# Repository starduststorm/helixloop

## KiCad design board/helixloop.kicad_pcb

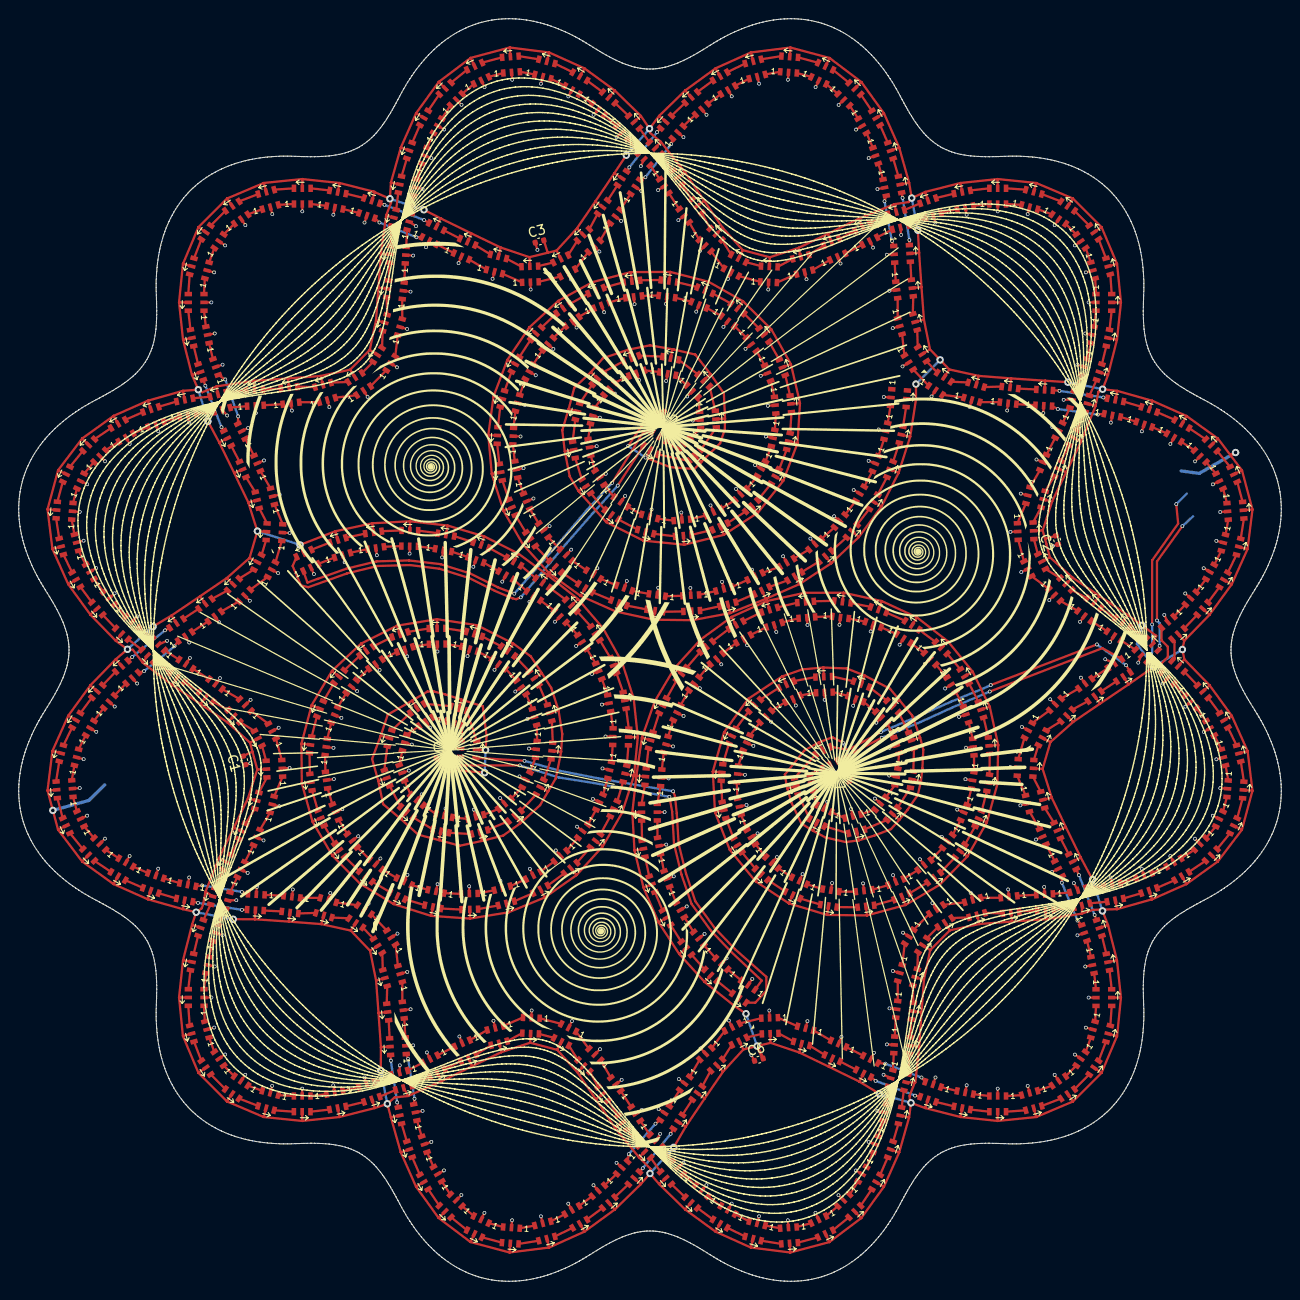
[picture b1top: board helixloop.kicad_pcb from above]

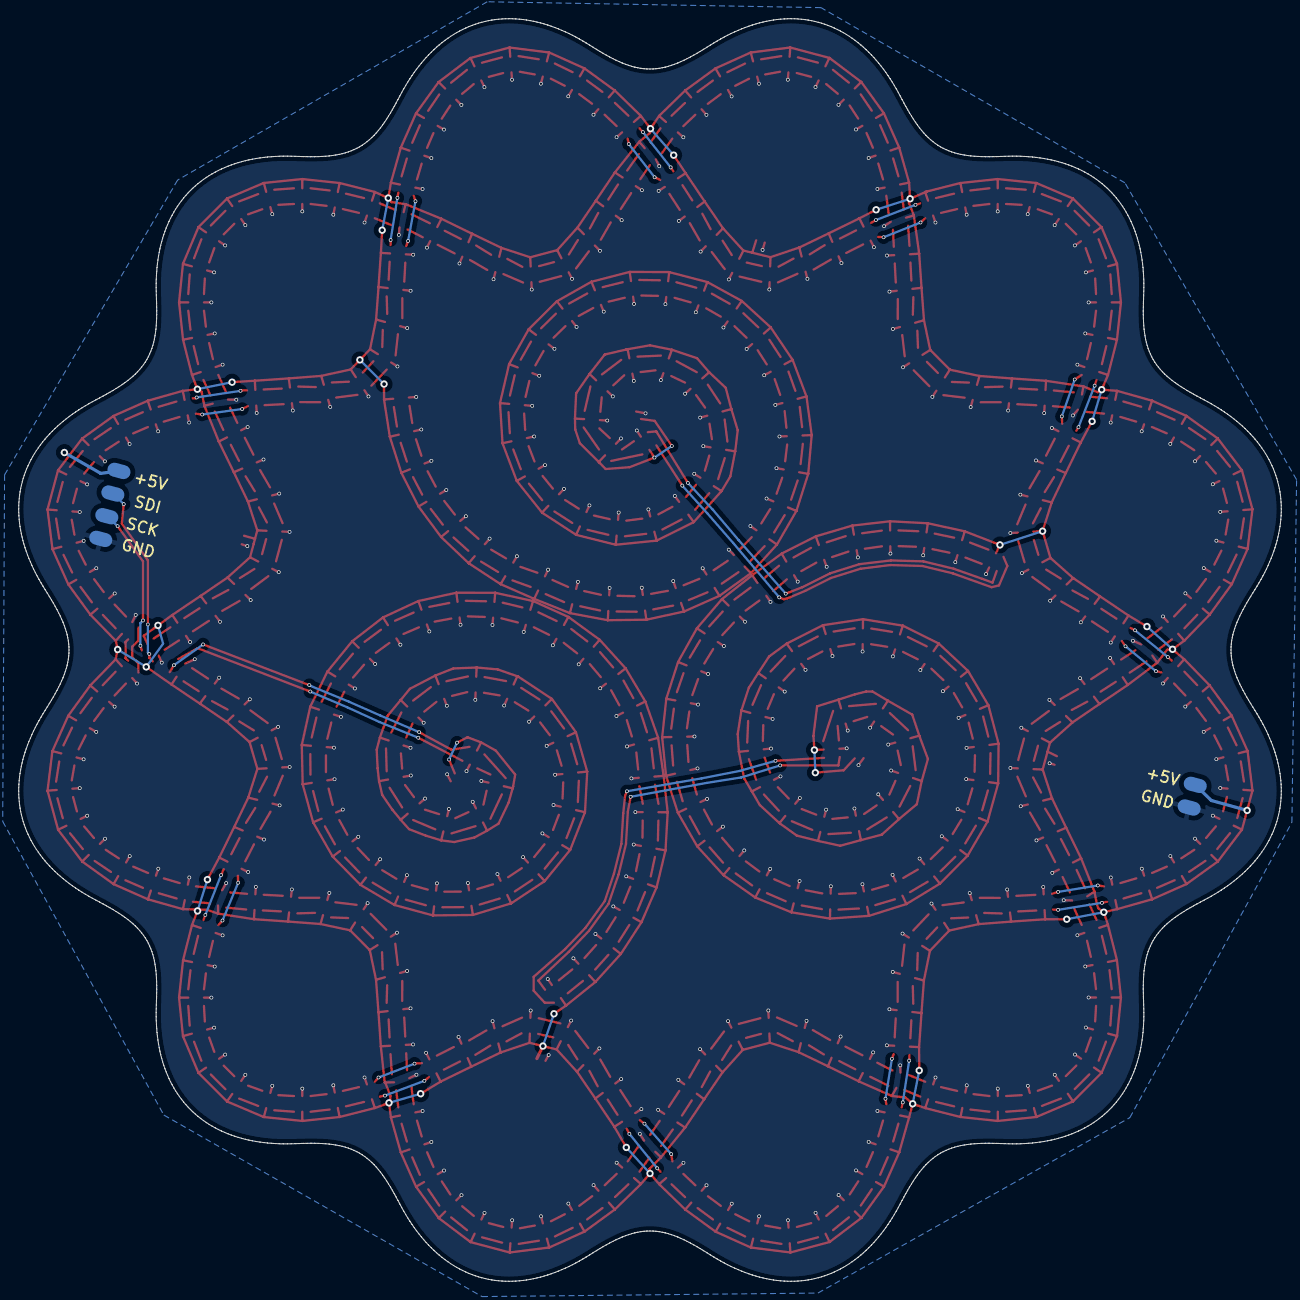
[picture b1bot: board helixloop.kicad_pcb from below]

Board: 2 copper layers, 136.7 x 136.7 mm, 379 parts (2 on the bottom side), 740 nets.

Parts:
C1, C2: 10uF; C_0402_1005Metric
C3, C4, C5, C6, C7: C_Small; C_0402_1005Metric
D1, D2, D3, D4, D5, D6, D7, D8, D9, D10, D11, D12, D13, D14, D15, D16, D17, D18, D19, D20, D21, D22, D23, D24, D25, D26, D27, D28, D29, D30, D31, D32, D33, D34, D35, D36, D37, D38, D39, D40, D41, D42, D43, D44, D45, D46, D47, D48, D49, D50, D51, D52, D53, D54, D55, D56, D57, D58, D59, D60, D61, D62, D63, D64, D65, D66, D67, D68, D69, D70, D71, D72, D73, D74, D75, D76, D77, D78, D79, D80, D81, D82, D83, D84, D85, D86, D87, D88, D89, D90, D91, D92, D93, D94, D95, D96, D97, D98, D99, D100, D101, D102, D103, D104, D105, D106, D107, D108, D109, D110, D111, D112, D113, D114, D115, D116, D117, D118, D119, D120, D121, D122, D123, D124, D125, D126, D127, D128, D129, D130, D131, D132, D133, D134, D135, D136, D137, D138, D139, D140, D141, D142, D143, D144, D145, D146, D147, D148, D149, D150, D151, D152, D153, D154, D155, D156, D157, D158, D159, D160, D161, D162, D163, D164, D165, D166, D167, D168, D169, D170, D171, D172, D173, D174, D175, D176, D177, D178, D179, D180, D181, D182, D183, D184, D185, D186, D187, D188, D189, D190, D191, D192, D193, D194, D195, D196, D197, D198, D199, D200, D201, D202, D203, D204, D205, D206, D207, D208, D209, D210, D211, D212, D213, D214, D215, D216, D217, D218, D219, D220, D221, D222, D223, D224, D225, D226, D227, D228, D229, D230, D231, D232, D233, D234, D235, D236, D237, D238, D239, D240, D241, D242, D243, D244, D245, D246, D247, D248, D249, D250, D251, D252, D253, D254, D255, D256, D257, D258, D259, D260, D261, D262, D263, D264, D265, D266, D267, D268, D269, D270, D271, D272, D273, D274, D275, D276, D277, D278, D279, D280, D281, D282, D283, D284, D285, D286, D287, D288, D289, D290, D291, D292, D293, D294, D295, D296, D297, D298, D299, D300, D301, D302, D303, D304, D305, D306, D307, D308, D309, D310, D311, D312, D313, D314, D315, D316, D317, D318, D319, D320, D321, D322, D323, D324, D325, D326, D327, D328, D329, D330, D331, D332, D333, D334, D335, D336, D337, D338, D339, D340, D341, D342, D343, D344, D345, D346, D347, D348, D349, D350, D351, D352, D353, D354, D355, D356, D357, D358, D359, D360, D361, D362, D363, D364, D365, D366, D367, D368, D369: SK9822-EC20; LED-SK9822-EC20
J1: Conn_01x04; SMD_Pad_01x04_2.54mm
J2: Conn_01x02; SMD_Pad_01x02_2.54mm
spiraldrawing: G***; spiraldrawing

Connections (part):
+5V: C1.2, C2.2, C3.2, C4.2, C5.2, C6.2, C7.2, D1.5 (VDD), D2.5 (VDD), D3.5 (VDD), D4.5 (VDD), D5.5 (VDD), D6.5 (VDD), D7.5 (VDD), D8.5 (VDD), D9.5 (VDD), D10.5 (VDD), D11.5 (VDD), D12.5 (VDD), D13.5 (VDD), D14.5 (VDD), D15.5 (VDD), D16.5 (VDD), D17.5 (VDD), D18.5 (VDD), D19.5 (VDD), D20.5 (VDD), D21.5 (VDD), D22.5 (VDD), D23.5 (VDD), D24.5 (VDD), D25.5 (VDD), D26.5 (VDD), D27.5 (VDD), D28.5 (VDD), D29.5 (VDD), D30.5 (VDD), D31.5 (VDD), D32.5 (VDD), D33.5 (VDD), D34.5 (VDD), D35.5 (VDD), D36.5 (VDD), D37.5 (VDD), D38.5 (VDD), D39.5 (VDD), D40.5 (VDD), D41.5 (VDD), D42.5 (VDD), D43.5 (VDD), D44.5 (VDD), D45.5 (VDD), D46.5 (VDD), D47.5 (VDD), D48.5 (VDD), D49.5 (VDD), D50.5 (VDD), D51.5 (VDD), D52.5 (VDD), D53.5 (VDD), D54.5 (VDD), D55.5 (VDD), D56.5 (VDD), D57.5 (VDD), D58.5 (VDD), D59.5 (VDD), D60.5 (VDD), D61.5 (VDD), D62.5 (VDD), D63.5 (VDD), D64.5 (VDD), D65.5 (VDD), D66.5 (VDD), D67.5 (VDD), D68.5 (VDD), D69.5 (VDD), D70.5 (VDD), D71.5 (VDD), D72.5 (VDD), D73.5 (VDD)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
/LED_CKI1: D1.4 (CKI), J1.3
/LED_SDI1: D1.3 (SDI), J1.2
/SK9822 LED Array 1/LED_CKO: D123.6 (CKO), D124.4 (CKI)
/SK9822 LED Array 1/LED_SDO: D123.1 (SDO), D124.3 (SDI)
/SK9822 LED Array 2/LED_CKO: D246.6 (CKO), D247.4 (CKI)
/SK9822 LED Array 2/LED_SDO: D246.1 (SDO), D247.3 (SDI)
GND: C1.1, C2.1, C3.1, C4.1, C5.1, C6.1, C7.1, D1.2 (GND), D2.2 (GND), D3.2 (GND), D4.2 (GND), D5.2 (GND), D6.2 (GND), D7.2 (GND), D8.2 (GND), D9.2 (GND), D10.2 (GND), D11.2 (GND), D12.2 (GND), D13.2 (GND), D14.2 (GND), D15.2 (GND), D16.2 (GND), D17.2 (GND), D18.2 (GND), D19.2 (GND), D20.2 (GND), D21.2 (GND), D22.2 (GND), D23.2 (GND), D24.2 (GND), D25.2 (GND), D26.2 (GND), D27.2 (GND), D28.2 (GND), D29.2 (GND), D30.2 (GND), D31.2 (GND), D32.2 (GND), D33.2 (GND), D34.2 (GND), D35.2 (GND), D36.2 (GND), D37.2 (GND), D38.2 (GND), D39.2 (GND), D40.2 (GND), D41.2 (GND), D42.2 (GND), D43.2 (GND), D44.2 (GND), D45.2 (GND), D46.2 (GND), D47.2 (GND), D48.2 (GND), D49.2 (GND), D50.2 (GND), D51.2 (GND), D52.2 (GND), D53.2 (GND), D54.2 (GND), D55.2 (GND), D56.2 (GND), D57.2 (GND), D58.2 (GND), D59.2 (GND), D60.2 (GND), D61.2 (GND), D62.2 (GND), D63.2 (GND), D64.2 (GND), D65.2 (GND), D66.2 (GND), D67.2 (GND), D68.2 (GND), D69.2 (GND), D70.2 (GND), D71.2 (GND), D72.2 (GND), D73.2 (GND)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
unnamed: D1.1 (SDO), D2.3 (SDI)
unnamed: D1.6 (CKO), D2.4 (CKI)
unnamed: D2.1 (SDO), D3.3 (SDI)
unnamed: D2.6 (CKO), D3.4 (CKI)
unnamed: D3.1 (SDO), D4.3 (SDI)
unnamed: D3.6 (CKO), D4.4 (CKI)
unnamed: D4.1 (SDO), D5.3 (SDI)
unnamed: D4.6 (CKO), D5.4 (CKI)
unnamed: D5.1 (SDO), D6.3 (SDI)
unnamed: D5.6 (CKO), D6.4 (CKI)
unnamed: D6.1 (SDO), D7.3 (SDI)
unnamed: D6.6 (CKO), D7.4 (CKI)
unnamed: D7.1 (SDO), D8.3 (SDI)
unnamed: D7.6 (CKO), D8.4 (CKI)
unnamed: D8.1 (SDO), D9.3 (SDI)
unnamed: D8.6 (CKO), D9.4 (CKI)
unnamed: D10.1 (SDO), D11.3 (SDI)
unnamed: D9.1 (SDO), D10.3 (SDI)
unnamed: D9.6 (CKO), D10.4 (CKI)
unnamed: D10.6 (CKO), D11.4 (CKI)
unnamed: D11.1 (SDO), D12.3 (SDI)
unnamed: D11.6 (CKO), D12.4 (CKI)
unnamed: D12.1 (SDO), D13.3 (SDI)
unnamed: D12.6 (CKO), D13.4 (CKI)
unnamed: D13.1 (SDO), D14.3 (SDI)
unnamed: D13.6 (CKO), D14.4 (CKI)
unnamed: D14.1 (SDO), D15.3 (SDI)
unnamed: D14.6 (CKO), D15.4 (CKI)
unnamed: D15.1 (SDO), D16.3 (SDI)
unnamed: D15.6 (CKO), D16.4 (CKI)
unnamed: D16.1 (SDO), D17.3 (SDI)
unnamed: D16.6 (CKO), D17.4 (CKI)
unnamed: D17.1 (SDO), D18.3 (SDI)
unnamed: D17.6 (CKO), D18.4 (CKI)
unnamed: D18.1 (SDO), D19.3 (SDI)
unnamed: D18.6 (CKO), D19.4 (CKI)
unnamed: D19.1 (SDO), D20.3 (SDI)
unnamed: D19.6 (CKO), D20.4 (CKI)
unnamed: D20.1 (SDO), D21.3 (SDI)
unnamed: D20.6 (CKO), D21.4 (CKI)
unnamed: D21.1 (SDO), D22.3 (SDI)
unnamed: D21.6 (CKO), D22.4 (CKI)
unnamed: D22.1 (SDO), D23.3 (SDI)
unnamed: D22.6 (CKO), D23.4 (CKI)
unnamed: D23.1 (SDO), D24.3 (SDI)
unnamed: D23.6 (CKO), D24.4 (CKI)
unnamed: D24.1 (SDO), D25.3 (SDI)
unnamed: D24.6 (CKO), D25.4 (CKI)
unnamed: D25.1 (SDO), D26.3 (SDI)
unnamed: D25.6 (CKO), D26.4 (CKI)
unnamed: D26.1 (SDO), D27.3 (SDI)
unnamed: D26.6 (CKO), D27.4 (CKI)
unnamed: D27.1 (SDO), D28.3 (SDI)
unnamed: D27.6 (CKO), D28.4 (CKI)
unnamed: D28.1 (SDO), D29.3 (SDI)
unnamed: D28.6 (CKO), D29.4 (CKI)
unnamed: D29.1 (SDO), D30.3 (SDI)
unnamed: D29.6 (CKO), D30.4 (CKI)
unnamed: D30.1 (SDO), D31.3 (SDI)
unnamed: D30.6 (CKO), D31.4 (CKI)
unnamed: D31.1 (SDO), D32.3 (SDI)
unnamed: D31.6 (CKO), D32.4 (CKI)
unnamed: D32.1 (SDO), D33.3 (SDI)
unnamed: D32.6 (CKO), D33.4 (CKI)
unnamed: D33.1 (SDO), D34.3 (SDI)
unnamed: D33.6 (CKO), D34.4 (CKI)
unnamed: D34.1 (SDO), D35.3 (SDI)
unnamed: D34.6 (CKO), D35.4 (CKI)
unnamed: D35.1 (SDO), D36.3 (SDI)
unnamed: D35.6 (CKO), D36.4 (CKI)
unnamed: D36.1 (SDO), D37.3 (SDI)
unnamed: D36.6 (CKO), D37.4 (CKI)
unnamed: D37.1 (SDO), D38.3 (SDI)
unnamed: D37.6 (CKO), D38.4 (CKI)
unnamed: D38.1 (SDO), D39.3 (SDI)
unnamed: D38.6 (CKO), D39.4 (CKI)
unnamed: D39.1 (SDO), D40.3 (SDI)
unnamed: D39.6 (CKO), D40.4 (CKI)
unnamed: D40.1 (SDO), D41.3 (SDI)
unnamed: D40.6 (CKO), D41.4 (CKI)
unnamed: D41.1 (SDO), D42.3 (SDI)
unnamed: D41.6 (CKO), D42.4 (CKI)
unnamed: D42.1 (SDO), D43.3 (SDI)
unnamed: D42.6 (CKO), D43.4 (CKI)
unnamed: D43.1 (SDO), D44.3 (SDI)
unnamed: D43.6 (CKO), D44.4 (CKI)
unnamed: D44.1 (SDO), D45.3 (SDI)
unnamed: D44.6 (CKO), D45.4 (CKI)
unnamed: D45.1 (SDO), D46.3 (SDI)
unnamed: D45.6 (CKO), D46.4 (CKI)
unnamed: D46.1 (SDO), D47.3 (SDI)
unnamed: D46.6 (CKO), D47.4 (CKI)
unnamed: D47.1 (SDO), D48.3 (SDI)
unnamed: D47.6 (CKO), D48.4 (CKI)
unnamed: D48.1 (SDO), D49.3 (SDI)
unnamed: D48.6 (CKO), D49.4 (CKI)
unnamed: D49.1 (SDO), D50.3 (SDI)
unnamed: D49.6 (CKO), D50.4 (CKI)
unnamed: D50.1 (SDO), D51.3 (SDI)
unnamed: D50.6 (CKO), D51.4 (CKI)
unnamed: D51.1 (SDO), D52.3 (SDI)
unnamed: D51.6 (CKO), D52.4 (CKI)
unnamed: D52.1 (SDO), D53.3 (SDI)
unnamed: D52.6 (CKO), D53.4 (CKI)
unnamed: D53.1 (SDO), D54.3 (SDI)
unnamed: D53.6 (CKO), D54.4 (CKI)
unnamed: D54.1 (SDO), D55.3 (SDI)
unnamed: D54.6 (CKO), D55.4 (CKI)
unnamed: D55.1 (SDO), D56.3 (SDI)
unnamed: D55.6 (CKO), D56.4 (CKI)
unnamed: D56.1 (SDO), D57.3 (SDI)
unnamed: D56.6 (CKO), D57.4 (CKI)
unnamed: D57.1 (SDO), D58.3 (SDI)
unnamed: D57.6 (CKO), D58.4 (CKI)
unnamed: D58.1 (SDO), D59.3 (SDI)
unnamed: D58.6 (CKO), D59.4 (CKI)
unnamed: D59.1 (SDO), D60.3 (SDI)
unnamed: D59.6 (CKO), D60.4 (CKI)
unnamed: D60.1 (SDO), D61.3 (SDI)
unnamed: D60.6 (CKO), D61.4 (CKI)
unnamed: D61.1 (SDO), D62.3 (SDI)
unnamed: D61.6 (CKO), D62.4 (CKI)
unnamed: D62.1 (SDO), D63.3 (SDI)
unnamed: D62.6 (CKO), D63.4 (CKI)
unnamed: D63.1 (SDO), D64.3 (SDI)
unnamed: D63.6 (CKO), D64.4 (CKI)
unnamed: D64.1 (SDO), D65.3 (SDI)
unnamed: D64.6 (CKO), D65.4 (CKI)
unnamed: D65.1 (SDO), D66.3 (SDI)
unnamed: D65.6 (CKO), D66.4 (CKI)
unnamed: D66.1 (SDO), D67.3 (SDI)
unnamed: D66.6 (CKO), D67.4 (CKI)
unnamed: D67.1 (SDO), D68.3 (SDI)
unnamed: D67.6 (CKO), D68.4 (CKI)
unnamed: D68.1 (SDO), D69.3 (SDI)
unnamed: D68.6 (CKO), D69.4 (CKI)
unnamed: D69.1 (SDO), D70.3 (SDI)
unnamed: D69.6 (CKO), D70.4 (CKI)
unnamed: D70.1 (SDO), D71.3 (SDI)
unnamed: D70.6 (CKO), D71.4 (CKI)
unnamed: D71.1 (SDO), D72.3 (SDI)
unnamed: D71.6 (CKO), D72.4 (CKI)
unnamed: D72.1 (SDO), D73.3 (SDI)
unnamed: D72.6 (CKO), D73.4 (CKI)
unnamed: D73.1 (SDO), D74.3 (SDI)
unnamed: D73.6 (CKO), D74.4 (CKI)
unnamed: D74.1 (SDO), D75.3 (SDI)
unnamed: D74.6 (CKO), D75.4 (CKI)
unnamed: D75.1 (SDO), D76.3 (SDI)
unnamed: D75.6 (CKO), D76.4 (CKI)
unnamed: D76.1 (SDO), D77.3 (SDI)
unnamed: D76.6 (CKO), D77.4 (CKI)
unnamed: D77.1 (SDO), D78.3 (SDI)
unnamed: D77.6 (CKO), D78.4 (CKI)
unnamed: D78.1 (SDO), D79.3 (SDI)
unnamed: D78.6 (CKO), D79.4 (CKI)
unnamed: D79.1 (SDO), D80.3 (SDI)
unnamed: D79.6 (CKO), D80.4 (CKI)
unnamed: D80.1 (SDO), D81.3 (SDI)
unnamed: D80.6 (CKO), D81.4 (CKI)
unnamed: D81.1 (SDO), D82.3 (SDI)
unnamed: D81.6 (CKO), D82.4 (CKI)
unnamed: D82.1 (SDO), D83.3 (SDI)
unnamed: D82.6 (CKO), D83.4 (CKI)
unnamed: D83.1 (SDO), D84.3 (SDI)
unnamed: D83.6 (CKO), D84.4 (CKI)
unnamed: D84.1 (SDO), D85.3 (SDI)
unnamed: D84.6 (CKO), D85.4 (CKI)
unnamed: D85.1 (SDO), D86.3 (SDI)
unnamed: D85.6 (CKO), D86.4 (CKI)
unnamed: D86.1 (SDO), D87.3 (SDI)
unnamed: D86.6 (CKO), D87.4 (CKI)
unnamed: D87.1 (SDO), D88.3 (SDI)
unnamed: D87.6 (CKO), D88.4 (CKI)
unnamed: D88.1 (SDO), D89.3 (SDI)
unnamed: D88.6 (CKO), D89.4 (CKI)
unnamed: D89.1 (SDO), D90.3 (SDI)
unnamed: D89.6 (CKO), D90.4 (CKI)
unnamed: D90.1 (SDO), D91.3 (SDI)
unnamed: D90.6 (CKO), D91.4 (CKI)
unnamed: D91.1 (SDO), D92.3 (SDI)
unnamed: D91.6 (CKO), D92.4 (CKI)
unnamed: D92.1 (SDO), D93.3 (SDI)
unnamed: D92.6 (CKO), D93.4 (CKI)
unnamed: D93.1 (SDO), D94.3 (SDI)
unnamed: D93.6 (CKO), D94.4 (CKI)
unnamed: D94.1 (SDO), D95.3 (SDI)
unnamed: D94.6 (CKO), D95.4 (CKI)
unnamed: D95.1 (SDO), D96.3 (SDI)
unnamed: D95.6 (CKO), D96.4 (CKI)
unnamed: D96.1 (SDO), D97.3 (SDI)
unnamed: D96.6 (CKO), D97.4 (CKI)
unnamed: D97.1 (SDO), D98.3 (SDI)
unnamed: D97.6 (CKO), D98.4 (CKI)
unnamed: D98.1 (SDO), D99.3 (SDI)
unnamed: D98.6 (CKO), D99.4 (CKI)
unnamed: D100.1 (SDO), D101.3 (SDI)
unnamed: D99.1 (SDO), D100.3 (SDI)
unnamed: D99.6 (CKO), D100.4 (CKI)
unnamed: D100.6 (CKO), D101.4 (CKI)
unnamed: D101.1 (SDO), D102.3 (SDI)
unnamed: D101.6 (CKO), D102.4 (CKI)
unnamed: D102.1 (SDO), D103.3 (SDI)
unnamed: D102.6 (CKO), D103.4 (CKI)
unnamed: D103.1 (SDO), D104.3 (SDI)
unnamed: D103.6 (CKO), D104.4 (CKI)
unnamed: D104.1 (SDO), D105.3 (SDI)
unnamed: D104.6 (CKO), D105.4 (CKI)
unnamed: D105.1 (SDO), D106.3 (SDI)
unnamed: D105.6 (CKO), D106.4 (CKI)
unnamed: D106.1 (SDO), D107.3 (SDI)
unnamed: D106.6 (CKO), D107.4 (CKI)
unnamed: D107.1 (SDO), D108.3 (SDI)
unnamed: D107.6 (CKO), D108.4 (CKI)
unnamed: D108.1 (SDO), D109.3 (SDI)
unnamed: D108.6 (CKO), D109.4 (CKI)
unnamed: D109.1 (SDO), D110.3 (SDI)
unnamed: D109.6 (CKO), D110.4 (CKI)
unnamed: D110.1 (SDO), D111.3 (SDI)
unnamed: D110.6 (CKO), D111.4 (CKI)
unnamed: D111.1 (SDO), D112.3 (SDI)
unnamed: D111.6 (CKO), D112.4 (CKI)
unnamed: D112.1 (SDO), D113.3 (SDI)
unnamed: D112.6 (CKO), D113.4 (CKI)
unnamed: D113.1 (SDO), D114.3 (SDI)
unnamed: D113.6 (CKO), D114.4 (CKI)
unnamed: D114.1 (SDO), D115.3 (SDI)
unnamed: D114.6 (CKO), D115.4 (CKI)
unnamed: D115.1 (SDO), D116.3 (SDI)
unnamed: D115.6 (CKO), D116.4 (CKI)
unnamed: D116.1 (SDO), D117.3 (SDI)
unnamed: D116.6 (CKO), D117.4 (CKI)
unnamed: D117.1 (SDO), D118.3 (SDI)
unnamed: D117.6 (CKO), D118.4 (CKI)
unnamed: D118.1 (SDO), D119.3 (SDI)
unnamed: D118.6 (CKO), D119.4 (CKI)
unnamed: D119.1 (SDO), D120.3 (SDI)
unnamed: D119.6 (CKO), D120.4 (CKI)
unnamed: D120.1 (SDO), D121.3 (SDI)
unnamed: D120.6 (CKO), D121.4 (CKI)
unnamed: D121.1 (SDO), D122.3 (SDI)
unnamed: D121.6 (CKO), D122.4 (CKI)
unnamed: D122.1 (SDO), D123.3 (SDI)
unnamed: D122.6 (CKO), D123.4 (CKI)
unnamed: D124.1 (SDO), D125.3 (SDI)
unnamed: D124.6 (CKO), D125.4 (CKI)
unnamed: D125.1 (SDO), D126.3 (SDI)
unnamed: D125.6 (CKO), D126.4 (CKI)
unnamed: D126.1 (SDO), D127.3 (SDI)
unnamed: D126.6 (CKO), D127.4 (CKI)
unnamed: D127.1 (SDO), D128.3 (SDI)
unnamed: D127.6 (CKO), D128.4 (CKI)
unnamed: D128.1 (SDO), D129.3 (SDI)
unnamed: D128.6 (CKO), D129.4 (CKI)
unnamed: D129.1 (SDO), D130.3 (SDI)
unnamed: D129.6 (CKO), D130.4 (CKI)
unnamed: D130.1 (SDO), D131.3 (SDI)
unnamed: D130.6 (CKO), D131.4 (CKI)
unnamed: D131.1 (SDO), D132.3 (SDI)
unnamed: D131.6 (CKO), D132.4 (CKI)
unnamed: D132.1 (SDO), D133.3 (SDI)
unnamed: D132.6 (CKO), D133.4 (CKI)
unnamed: D133.1 (SDO), D134.3 (SDI)
unnamed: D133.6 (CKO), D134.4 (CKI)
unnamed: D134.1 (SDO), D135.3 (SDI)
unnamed: D134.6 (CKO), D135.4 (CKI)
unnamed: D135.1 (SDO), D136.3 (SDI)
unnamed: D135.6 (CKO), D136.4 (CKI)
unnamed: D136.1 (SDO), D137.3 (SDI)
unnamed: D136.6 (CKO), D137.4 (CKI)
unnamed: D137.1 (SDO), D138.3 (SDI)
unnamed: D137.6 (CKO), D138.4 (CKI)
unnamed: D138.1 (SDO), D139.3 (SDI)
unnamed: D138.6 (CKO), D139.4 (CKI)
unnamed: D139.1 (SDO), D140.3 (SDI)
unnamed: D139.6 (CKO), D140.4 (CKI)
unnamed: D140.1 (SDO), D141.3 (SDI)
unnamed: D140.6 (CKO), D141.4 (CKI)
unnamed: D141.1 (SDO), D142.3 (SDI)
unnamed: D141.6 (CKO), D142.4 (CKI)
unnamed: D142.1 (SDO), D143.3 (SDI)
unnamed: D142.6 (CKO), D143.4 (CKI)
unnamed: D143.1 (SDO), D144.3 (SDI)
unnamed: D143.6 (CKO), D144.4 (CKI)
unnamed: D144.1 (SDO), D145.3 (SDI)
unnamed: D144.6 (CKO), D145.4 (CKI)
unnamed: D145.1 (SDO), D146.3 (SDI)
unnamed: D145.6 (CKO), D146.4 (CKI)
unnamed: D146.1 (SDO), D147.3 (SDI)
unnamed: D146.6 (CKO), D147.4 (CKI)
unnamed: D147.1 (SDO), D148.3 (SDI)
unnamed: D147.6 (CKO), D148.4 (CKI)
unnamed: D148.1 (SDO), D149.3 (SDI)
unnamed: D148.6 (CKO), D149.4 (CKI)
unnamed: D149.1 (SDO), D150.3 (SDI)
unnamed: D149.6 (CKO), D150.4 (CKI)
unnamed: D150.1 (SDO), D151.3 (SDI)
unnamed: D150.6 (CKO), D151.4 (CKI)
unnamed: D151.1 (SDO), D152.3 (SDI)
unnamed: D151.6 (CKO), D152.4 (CKI)
unnamed: D152.1 (SDO), D153.3 (SDI)
unnamed: D152.6 (CKO), D153.4 (CKI)
unnamed: D153.1 (SDO), D154.3 (SDI)
unnamed: D153.6 (CKO), D154.4 (CKI)
unnamed: D154.1 (SDO), D155.3 (SDI)
unnamed: D154.6 (CKO), D155.4 (CKI)
unnamed: D155.1 (SDO), D156.3 (SDI)
unnamed: D155.6 (CKO), D156.4 (CKI)
unnamed: D156.1 (SDO), D157.3 (SDI)
unnamed: D156.6 (CKO), D157.4 (CKI)
unnamed: D157.1 (SDO), D158.3 (SDI)
unnamed: D157.6 (CKO), D158.4 (CKI)
unnamed: D158.1 (SDO), D159.3 (SDI)
unnamed: D158.6 (CKO), D159.4 (CKI)
unnamed: D159.1 (SDO), D160.3 (SDI)
unnamed: D159.6 (CKO), D160.4 (CKI)
unnamed: D160.1 (SDO), D161.3 (SDI)
unnamed: D160.6 (CKO), D161.4 (CKI)
unnamed: D161.1 (SDO), D162.3 (SDI)
unnamed: D161.6 (CKO), D162.4 (CKI)
unnamed: D162.1 (SDO), D163.3 (SDI)
unnamed: D162.6 (CKO), D163.4 (CKI)
unnamed: D163.1 (SDO), D164.3 (SDI)
unnamed: D163.6 (CKO), D164.4 (CKI)
unnamed: D164.1 (SDO), D165.3 (SDI)
unnamed: D164.6 (CKO), D165.4 (CKI)
unnamed: D165.1 (SDO), D166.3 (SDI)
unnamed: D165.6 (CKO), D166.4 (CKI)
unnamed: D166.1 (SDO), D167.3 (SDI)
unnamed: D166.6 (CKO), D167.4 (CKI)
unnamed: D167.1 (SDO), D168.3 (SDI)
unnamed: D167.6 (CKO), D168.4 (CKI)
unnamed: D168.1 (SDO), D169.3 (SDI)
unnamed: D168.6 (CKO), D169.4 (CKI)
unnamed: D169.1 (SDO), D170.3 (SDI)
unnamed: D169.6 (CKO), D170.4 (CKI)
unnamed: D170.1 (SDO), D171.3 (SDI)
unnamed: D170.6 (CKO), D171.4 (CKI)
unnamed: D171.1 (SDO), D172.3 (SDI)
unnamed: D171.6 (CKO), D172.4 (CKI)
unnamed: D172.1 (SDO), D173.3 (SDI)
unnamed: D172.6 (CKO), D173.4 (CKI)
unnamed: D173.1 (SDO), D174.3 (SDI)
unnamed: D173.6 (CKO), D174.4 (CKI)
unnamed: D174.1 (SDO), D175.3 (SDI)
unnamed: D174.6 (CKO), D175.4 (CKI)
unnamed: D175.1 (SDO), D176.3 (SDI)
unnamed: D175.6 (CKO), D176.4 (CKI)
unnamed: D176.1 (SDO), D177.3 (SDI)
unnamed: D176.6 (CKO), D177.4 (CKI)
unnamed: D177.1 (SDO), D178.3 (SDI)
unnamed: D177.6 (CKO), D178.4 (CKI)
unnamed: D178.1 (SDO), D179.3 (SDI)
unnamed: D178.6 (CKO), D179.4 (CKI)
unnamed: D179.1 (SDO), D180.3 (SDI)
unnamed: D179.6 (CKO), D180.4 (CKI)
unnamed: D180.1 (SDO), D181.3 (SDI)
unnamed: D180.6 (CKO), D181.4 (CKI)
unnamed: D181.1 (SDO), D182.3 (SDI)
unnamed: D181.6 (CKO), D182.4 (CKI)
unnamed: D182.1 (SDO), D183.3 (SDI)
unnamed: D182.6 (CKO), D183.4 (CKI)
unnamed: D183.1 (SDO), D184.3 (SDI)
unnamed: D183.6 (CKO), D184.4 (CKI)
unnamed: D184.1 (SDO), D185.3 (SDI)
unnamed: D184.6 (CKO), D185.4 (CKI)
unnamed: D185.1 (SDO), D186.3 (SDI)
unnamed: D185.6 (CKO), D186.4 (CKI)
unnamed: D186.1 (SDO), D187.3 (SDI)
unnamed: D186.6 (CKO), D187.4 (CKI)
unnamed: D187.1 (SDO), D188.3 (SDI)
unnamed: D187.6 (CKO), D188.4 (CKI)
unnamed: D188.1 (SDO), D189.3 (SDI)
unnamed: D188.6 (CKO), D189.4 (CKI)
unnamed: D189.1 (SDO), D190.3 (SDI)
unnamed: D189.6 (CKO), D190.4 (CKI)
unnamed: D190.1 (SDO), D191.3 (SDI)
unnamed: D190.6 (CKO), D191.4 (CKI)
unnamed: D191.1 (SDO), D192.3 (SDI)
unnamed: D191.6 (CKO), D192.4 (CKI)
unnamed: D192.1 (SDO), D193.3 (SDI)
unnamed: D192.6 (CKO), D193.4 (CKI)
unnamed: D193.1 (SDO), D194.3 (SDI)
unnamed: D193.6 (CKO), D194.4 (CKI)
unnamed: D194.1 (SDO), D195.3 (SDI)
unnamed: D194.6 (CKO), D195.4 (CKI)
unnamed: D195.1 (SDO), D196.3 (SDI)
unnamed: D195.6 (CKO), D196.4 (CKI)
unnamed: D196.1 (SDO), D197.3 (SDI)
unnamed: D196.6 (CKO), D197.4 (CKI)
unnamed: D197.1 (SDO), D198.3 (SDI)
unnamed: D197.6 (CKO), D198.4 (CKI)
unnamed: D198.1 (SDO), D199.3 (SDI)
unnamed: D198.6 (CKO), D199.4 (CKI)
unnamed: D199.1 (SDO), D200.3 (SDI)
unnamed: D199.6 (CKO), D200.4 (CKI)
unnamed: D200.1 (SDO), D201.3 (SDI)
unnamed: D200.6 (CKO), D201.4 (CKI)
unnamed: D201.1 (SDO), D202.3 (SDI)
unnamed: D201.6 (CKO), D202.4 (CKI)
unnamed: D202.1 (SDO), D203.3 (SDI)
unnamed: D202.6 (CKO), D203.4 (CKI)
unnamed: D203.1 (SDO), D204.3 (SDI)
unnamed: D203.6 (CKO), D204.4 (CKI)
unnamed: D204.1 (SDO), D205.3 (SDI)
unnamed: D204.6 (CKO), D205.4 (CKI)
unnamed: D205.1 (SDO), D206.3 (SDI)
unnamed: D205.6 (CKO), D206.4 (CKI)
unnamed: D206.1 (SDO), D207.3 (SDI)
unnamed: D206.6 (CKO), D207.4 (CKI)
unnamed: D207.1 (SDO), D208.3 (SDI)
unnamed: D207.6 (CKO), D208.4 (CKI)
unnamed: D208.1 (SDO), D209.3 (SDI)
unnamed: D208.6 (CKO), D209.4 (CKI)
unnamed: D209.1 (SDO), D210.3 (SDI)
unnamed: D209.6 (CKO), D210.4 (CKI)
unnamed: D210.1 (SDO), D211.3 (SDI)
unnamed: D210.6 (CKO), D211.4 (CKI)
unnamed: D211.1 (SDO), D212.3 (SDI)
unnamed: D211.6 (CKO), D212.4 (CKI)
unnamed: D212.1 (SDO), D213.3 (SDI)
unnamed: D212.6 (CKO), D213.4 (CKI)
unnamed: D213.1 (SDO), D214.3 (SDI)
unnamed: D213.6 (CKO), D214.4 (CKI)
unnamed: D214.1 (SDO), D215.3 (SDI)
unnamed: D214.6 (CKO), D215.4 (CKI)
unnamed: D215.1 (SDO), D216.3 (SDI)
unnamed: D215.6 (CKO), D216.4 (CKI)
unnamed: D216.1 (SDO), D217.3 (SDI)
unnamed: D216.6 (CKO), D217.4 (CKI)
unnamed: D217.1 (SDO), D218.3 (SDI)
unnamed: D217.6 (CKO), D218.4 (CKI)
unnamed: D218.1 (SDO), D219.3 (SDI)
unnamed: D218.6 (CKO), D219.4 (CKI)
unnamed: D219.1 (SDO), D220.3 (SDI)
unnamed: D219.6 (CKO), D220.4 (CKI)
unnamed: D220.1 (SDO), D221.3 (SDI)
unnamed: D220.6 (CKO), D221.4 (CKI)
unnamed: D221.1 (SDO), D222.3 (SDI)
unnamed: D221.6 (CKO), D222.4 (CKI)
unnamed: D222.1 (SDO), D223.3 (SDI)
unnamed: D222.6 (CKO), D223.4 (CKI)
unnamed: D223.1 (SDO), D224.3 (SDI)
unnamed: D223.6 (CKO), D224.4 (CKI)
unnamed: D224.1 (SDO), D225.3 (SDI)
unnamed: D224.6 (CKO), D225.4 (CKI)
unnamed: D225.1 (SDO), D226.3 (SDI)
unnamed: D225.6 (CKO), D226.4 (CKI)
unnamed: D226.1 (SDO), D227.3 (SDI)
unnamed: D226.6 (CKO), D227.4 (CKI)
unnamed: D227.1 (SDO), D228.3 (SDI)
unnamed: D227.6 (CKO), D228.4 (CKI)
unnamed: D228.1 (SDO), D229.3 (SDI)
unnamed: D228.6 (CKO), D229.4 (CKI)
unnamed: D229.1 (SDO), D230.3 (SDI)
unnamed: D229.6 (CKO), D230.4 (CKI)
unnamed: D230.1 (SDO), D231.3 (SDI)
unnamed: D230.6 (CKO), D231.4 (CKI)
unnamed: D231.1 (SDO), D232.3 (SDI)
unnamed: D231.6 (CKO), D232.4 (CKI)
unnamed: D232.1 (SDO), D233.3 (SDI)
unnamed: D232.6 (CKO), D233.4 (CKI)
unnamed: D233.1 (SDO), D234.3 (SDI)
unnamed: D233.6 (CKO), D234.4 (CKI)
unnamed: D234.1 (SDO), D235.3 (SDI)
unnamed: D234.6 (CKO), D235.4 (CKI)
unnamed: D235.1 (SDO), D236.3 (SDI)
unnamed: D235.6 (CKO), D236.4 (CKI)
unnamed: D236.1 (SDO), D237.3 (SDI)
unnamed: D236.6 (CKO), D237.4 (CKI)
unnamed: D237.1 (SDO), D238.3 (SDI)
unnamed: D237.6 (CKO), D238.4 (CKI)
unnamed: D238.1 (SDO), D239.3 (SDI)
unnamed: D238.6 (CKO), D239.4 (CKI)
unnamed: D239.1 (SDO), D240.3 (SDI)
unnamed: D239.6 (CKO), D240.4 (CKI)
unnamed: D240.1 (SDO), D241.3 (SDI)
unnamed: D240.6 (CKO), D241.4 (CKI)
unnamed: D241.1 (SDO), D242.3 (SDI)
unnamed: D241.6 (CKO), D242.4 (CKI)
unnamed: D242.1 (SDO), D243.3 (SDI)
unnamed: D242.6 (CKO), D243.4 (CKI)
unnamed: D243.1 (SDO), D244.3 (SDI)
unnamed: D243.6 (CKO), D244.4 (CKI)
unnamed: D244.1 (SDO), D245.3 (SDI)
unnamed: D244.6 (CKO), D245.4 (CKI)
unnamed: D245.1 (SDO), D246.3 (SDI)
unnamed: D245.6 (CKO), D246.4 (CKI)
unnamed: D247.1 (SDO), D248.3 (SDI)
unnamed: D247.6 (CKO), D248.4 (CKI)
unnamed: D248.1 (SDO), D249.3 (SDI)
unnamed: D248.6 (CKO), D249.4 (CKI)
unnamed: D249.1 (SDO), D250.3 (SDI)
unnamed: D249.6 (CKO), D250.4 (CKI)
unnamed: D250.1 (SDO), D251.3 (SDI)
unnamed: D250.6 (CKO), D251.4 (CKI)
unnamed: D251.1 (SDO), D252.3 (SDI)
unnamed: D251.6 (CKO), D252.4 (CKI)
unnamed: D252.1 (SDO), D253.3 (SDI)
unnamed: D252.6 (CKO), D253.4 (CKI)
unnamed: D253.1 (SDO), D254.3 (SDI)
unnamed: D253.6 (CKO), D254.4 (CKI)
unnamed: D254.1 (SDO), D255.3 (SDI)
unnamed: D254.6 (CKO), D255.4 (CKI)
unnamed: D255.1 (SDO), D256.3 (SDI)
unnamed: D255.6 (CKO), D256.4 (CKI)
unnamed: D256.1 (SDO), D257.3 (SDI)
unnamed: D256.6 (CKO), D257.4 (CKI)
unnamed: D257.1 (SDO), D258.3 (SDI)
unnamed: D257.6 (CKO), D258.4 (CKI)
unnamed: D258.1 (SDO), D259.3 (SDI)
unnamed: D258.6 (CKO), D259.4 (CKI)
unnamed: D259.1 (SDO), D260.3 (SDI)
unnamed: D259.6 (CKO), D260.4 (CKI)
unnamed: D260.1 (SDO), D261.3 (SDI)
unnamed: D260.6 (CKO), D261.4 (CKI)
unnamed: D261.1 (SDO), D262.3 (SDI)
unnamed: D261.6 (CKO), D262.4 (CKI)
unnamed: D262.1 (SDO), D263.3 (SDI)
unnamed: D262.6 (CKO), D263.4 (CKI)
unnamed: D263.1 (SDO), D264.3 (SDI)
unnamed: D263.6 (CKO), D264.4 (CKI)
unnamed: D264.1 (SDO), D265.3 (SDI)
unnamed: D264.6 (CKO), D265.4 (CKI)
unnamed: D265.1 (SDO), D266.3 (SDI)
unnamed: D265.6 (CKO), D266.4 (CKI)
unnamed: D266.1 (SDO), D267.3 (SDI)
unnamed: D266.6 (CKO), D267.4 (CKI)
unnamed: D267.1 (SDO), D268.3 (SDI)
unnamed: D267.6 (CKO), D268.4 (CKI)
unnamed: D268.1 (SDO), D269.3 (SDI)
unnamed: D268.6 (CKO), D269.4 (CKI)
unnamed: D269.1 (SDO), D270.3 (SDI)
unnamed: D269.6 (CKO), D270.4 (CKI)
unnamed: D270.1 (SDO), D271.3 (SDI)
unnamed: D270.6 (CKO), D271.4 (CKI)
unnamed: D271.1 (SDO), D272.3 (SDI)
unnamed: D271.6 (CKO), D272.4 (CKI)
unnamed: D272.1 (SDO), D273.3 (SDI)
unnamed: D272.6 (CKO), D273.4 (CKI)
unnamed: D273.1 (SDO), D274.3 (SDI)
unnamed: D273.6 (CKO), D274.4 (CKI)
unnamed: D274.1 (SDO), D275.3 (SDI)
unnamed: D274.6 (CKO), D275.4 (CKI)
unnamed: D275.1 (SDO), D276.3 (SDI)
unnamed: D275.6 (CKO), D276.4 (CKI)
unnamed: D276.1 (SDO), D277.3 (SDI)
unnamed: D276.6 (CKO), D277.4 (CKI)
unnamed: D277.1 (SDO), D278.3 (SDI)
unnamed: D277.6 (CKO), D278.4 (CKI)
unnamed: D278.1 (SDO), D279.3 (SDI)
unnamed: D278.6 (CKO), D279.4 (CKI)
unnamed: D279.1 (SDO), D280.3 (SDI)
unnamed: D279.6 (CKO), D280.4 (CKI)
unnamed: D280.1 (SDO), D281.3 (SDI)
unnamed: D280.6 (CKO), D281.4 (CKI)
unnamed: D281.1 (SDO), D282.3 (SDI)
unnamed: D281.6 (CKO), D282.4 (CKI)
unnamed: D282.1 (SDO), D283.3 (SDI)
unnamed: D282.6 (CKO), D283.4 (CKI)
unnamed: D283.1 (SDO), D284.3 (SDI)
unnamed: D283.6 (CKO), D284.4 (CKI)
unnamed: D284.1 (SDO), D285.3 (SDI)
unnamed: D284.6 (CKO), D285.4 (CKI)
unnamed: D285.1 (SDO), D286.3 (SDI)
unnamed: D285.6 (CKO), D286.4 (CKI)
unnamed: D286.1 (SDO), D287.3 (SDI)
unnamed: D286.6 (CKO), D287.4 (CKI)
unnamed: D287.1 (SDO), D288.3 (SDI)
unnamed: D287.6 (CKO), D288.4 (CKI)
unnamed: D288.1 (SDO), D289.3 (SDI)
unnamed: D288.6 (CKO), D289.4 (CKI)
unnamed: D289.1 (SDO), D290.3 (SDI)
unnamed: D289.6 (CKO), D290.4 (CKI)
unnamed: D290.1 (SDO), D291.3 (SDI)
unnamed: D290.6 (CKO), D291.4 (CKI)
unnamed: D291.1 (SDO), D292.3 (SDI)
unnamed: D291.6 (CKO), D292.4 (CKI)
unnamed: D292.1 (SDO), D293.3 (SDI)
unnamed: D292.6 (CKO), D293.4 (CKI)
unnamed: D293.1 (SDO), D294.3 (SDI)
unnamed: D293.6 (CKO), D294.4 (CKI)
unnamed: D294.1 (SDO), D295.3 (SDI)
unnamed: D294.6 (CKO), D295.4 (CKI)
unnamed: D295.1 (SDO), D296.3 (SDI)
unnamed: D295.6 (CKO), D296.4 (CKI)
unnamed: D296.1 (SDO), D297.3 (SDI)
unnamed: D296.6 (CKO), D297.4 (CKI)
unnamed: D297.1 (SDO), D298.3 (SDI)
unnamed: D297.6 (CKO), D298.4 (CKI)
unnamed: D298.1 (SDO), D299.3 (SDI)
unnamed: D298.6 (CKO), D299.4 (CKI)
unnamed: D299.1 (SDO), D300.3 (SDI)
unnamed: D299.6 (CKO), D300.4 (CKI)
unnamed: D300.1 (SDO), D301.3 (SDI)
unnamed: D300.6 (CKO), D301.4 (CKI)
unnamed: D301.1 (SDO), D302.3 (SDI)
unnamed: D301.6 (CKO), D302.4 (CKI)
unnamed: D302.1 (SDO), D303.3 (SDI)
unnamed: D302.6 (CKO), D303.4 (CKI)
unnamed: D303.1 (SDO), D304.3 (SDI)
unnamed: D303.6 (CKO), D304.4 (CKI)
unnamed: D304.1 (SDO), D305.3 (SDI)
unnamed: D304.6 (CKO), D305.4 (CKI)
unnamed: D305.1 (SDO), D306.3 (SDI)
unnamed: D305.6 (CKO), D306.4 (CKI)
unnamed: D306.1 (SDO), D307.3 (SDI)
unnamed: D306.6 (CKO), D307.4 (CKI)
unnamed: D307.1 (SDO), D308.3 (SDI)
unnamed: D307.6 (CKO), D308.4 (CKI)
unnamed: D308.1 (SDO), D309.3 (SDI)
unnamed: D308.6 (CKO), D309.4 (CKI)
unnamed: D309.1 (SDO), D310.3 (SDI)
unnamed: D309.6 (CKO), D310.4 (CKI)
unnamed: D310.1 (SDO), D311.3 (SDI)
unnamed: D310.6 (CKO), D311.4 (CKI)
unnamed: D311.1 (SDO), D312.3 (SDI)
unnamed: D311.6 (CKO), D312.4 (CKI)
unnamed: D312.1 (SDO), D313.3 (SDI)
unnamed: D312.6 (CKO), D313.4 (CKI)
unnamed: D313.1 (SDO), D314.3 (SDI)
unnamed: D313.6 (CKO), D314.4 (CKI)
unnamed: D314.1 (SDO), D315.3 (SDI)
unnamed: D314.6 (CKO), D315.4 (CKI)
unnamed: D315.1 (SDO), D316.3 (SDI)
unnamed: D315.6 (CKO), D316.4 (CKI)
unnamed: D316.1 (SDO), D317.3 (SDI)
unnamed: D316.6 (CKO), D317.4 (CKI)
unnamed: D317.1 (SDO), D318.3 (SDI)
unnamed: D317.6 (CKO), D318.4 (CKI)
unnamed: D318.1 (SDO), D319.3 (SDI)
unnamed: D318.6 (CKO), D319.4 (CKI)
unnamed: D319.1 (SDO), D320.3 (SDI)
unnamed: D319.6 (CKO), D320.4 (CKI)
unnamed: D320.1 (SDO), D321.3 (SDI)
unnamed: D320.6 (CKO), D321.4 (CKI)
unnamed: D321.1 (SDO), D322.3 (SDI)
unnamed: D321.6 (CKO), D322.4 (CKI)
unnamed: D322.1 (SDO), D323.3 (SDI)
unnamed: D322.6 (CKO), D323.4 (CKI)
unnamed: D323.1 (SDO), D324.3 (SDI)
unnamed: D323.6 (CKO), D324.4 (CKI)
unnamed: D324.1 (SDO), D325.3 (SDI)
unnamed: D324.6 (CKO), D325.4 (CKI)
unnamed: D325.1 (SDO), D326.3 (SDI)
unnamed: D325.6 (CKO), D326.4 (CKI)
unnamed: D326.1 (SDO), D327.3 (SDI)
unnamed: D326.6 (CKO), D327.4 (CKI)
unnamed: D327.1 (SDO), D328.3 (SDI)
unnamed: D327.6 (CKO), D328.4 (CKI)
unnamed: D328.1 (SDO), D329.3 (SDI)
unnamed: D328.6 (CKO), D329.4 (CKI)
unnamed: D329.1 (SDO), D330.3 (SDI)
unnamed: D329.6 (CKO), D330.4 (CKI)
unnamed: D330.1 (SDO), D331.3 (SDI)
unnamed: D330.6 (CKO), D331.4 (CKI)
unnamed: D331.1 (SDO), D332.3 (SDI)
unnamed: D331.6 (CKO), D332.4 (CKI)
unnamed: D332.1 (SDO), D333.3 (SDI)
unnamed: D332.6 (CKO), D333.4 (CKI)
unnamed: D333.1 (SDO), D334.3 (SDI)
unnamed: D333.6 (CKO), D334.4 (CKI)
unnamed: D334.1 (SDO), D335.3 (SDI)
unnamed: D334.6 (CKO), D335.4 (CKI)
unnamed: D335.1 (SDO), D336.3 (SDI)
unnamed: D335.6 (CKO), D336.4 (CKI)
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
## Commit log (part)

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2022-07-23 first commit for candidate pixel layout for helixloop project; cribbed layout code from evm, refactored & updated for kicad 6
2022-07-29 a rather awesome revision
2022-07-29 tweaks; make layout script
2022-07-29 fix segment drawing
2022-08-07 adopt SK9822-EC20 led with a custom footprint; this changes the pixel spacing I thought I had, and now I want to tighten it
2022-08-17 tighten pixel spacing by shrinking the entire design slightly; improve pixel layout using a square footprint; but: there's a way to make this easier
2022-08-18 tweaks to spiral layout to settle on 369 pixels and align with helix
2022-08-18 improve edge cuts shape
2022-08-24 add a spiral drawing created & imported from svg
2022-08-25 extend pixel-spiral line decoration outside the spiral and clip it really nicely along the helix
2022-08-25 change spiral svg to have variable-size stroke; fiddle with inkscape and svg2mod entirely too long to get this to work as a kicad footprint
2022-08-25 tweaks to spiral bars, plus a concept for decorating the outer helix
2022-08-28 lower number of points used in spiral drawing by a factor of 8 since it was slowing down kicad; also lower point count in helix drawing
2022-08-30 only draw half of the helix decorations because it looks cooler
2022-09-02 create a bare schematic for 369 leds and some smd pads; change spiral layout so that there are actually 369 leds (we were skipping indexes on overlaps); fix pixel trace positions on overlap; fix pixe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
2022-09-05 refine the edge.cuts to be nice and smooth
2022-09-07 finally get pixels all aligned right by laying out the sine-wave in chunks and using different pixel spacing for outer vs inner curve
2022-09-07 programmatically draw traces to roughly connect +5V lines
2022-09-07 draft routing
2022-09-08 add some labels to the back
2022-09-08 fix the SK9822-EC20 footprint, which wasn't to spec for some reason? sprinkle in capacitors in a more decorative arrangement; add a mounting hole in the center; fix all ERC errors
2022-09-08 additional tweak to footprint; hide a reference designator; tweaks to hopefully improve electrical flow i.e. widen some traces; put kicad_prl in the .gitignore corner
2022-09-08 annotate capacitors as 10uF
2022-09-24 add an untested ledgraph for helixloop pixel layout
2022-09-24 crib some code, also untested, from evm
2022-10-25 progress checkpoint: new edge types to support new pixel layout; pixel layout is correct afaik; two-byte pixel indexes; bubble up the Edge object to BitsFiller rather than just indexes to prep for mo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
2022-11-13 FASTLED_USE_GLOBAL_BRIGHTNESS 1; and name SwarmPattern
2023-05-10 add a number of scad files and 3d models for parts used to build a rotating, projecting platform for the led board
2023-05-10 bug fix in my wc
2023-05-10 add support for seeed xiao with an attached 28BYJ-48 motor
2023-05-10 add a new test pattern using some more complex navigation based on EdgeTypesQuad and some in-pattern logic
2023-05-11 start off from a random state
2023-07-25 remove unused line
2023-10-11 add a new pattern. it's pretty
2025-09-08 partial dustlib adoption; add seeed rp2040 target
2025-10-31 update to kicad 8 format
2025-11-06 v2 concept: add an rp2040, microphone, usb port; rotate entire design 1/12 turn to help align usb port and led data in; rough layout
2025-11-25 add a 5v copper layer on top; add more 5v capacitance; layout improvements
2025-11-25 mostly fix ERC
2025-11-25 add 3 touch points
2025-11-25 touchpoint footprint
2025-11-25 add spiral drawing back in and remove homedir path; fix mic symbol link
2025-11-25 export swd pins and all four analog pins to small tht connectors; tweak back-copper gnd fill margins
2025-11-25 add pixel 3d model
2025-11-25 add more mounting holes
2025-11-27 add sds text and logo
2025-11-27 minor layout tweaks around pinouts and touch pads
2025-11-27 rotate the pixel footprint by -90deg so that it matches JLC's default orientation
2025-11-27 move pin labels up to match moved connector
2026-01-21 v2 bringup
2026-01-21 fix an ledgraph issue and make palette color selections consistent
2026-01-23 last commit was actually mostly to adopt Graph and ParticleSim from dustlib and remove all the old BitsFiller code; this commit is playing with new Particles features and adopting some brand new ones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
